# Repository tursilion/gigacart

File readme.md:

20181211

This is a largely unsorted folder that contains all source for TI-99/4A Dragon's Lair (but no copyrighted video, sorry), test code, PCB layouts for KiCad and CPLD programming for the Gigacart it ran on.

It's on the 'contact me and ask' license. ;)

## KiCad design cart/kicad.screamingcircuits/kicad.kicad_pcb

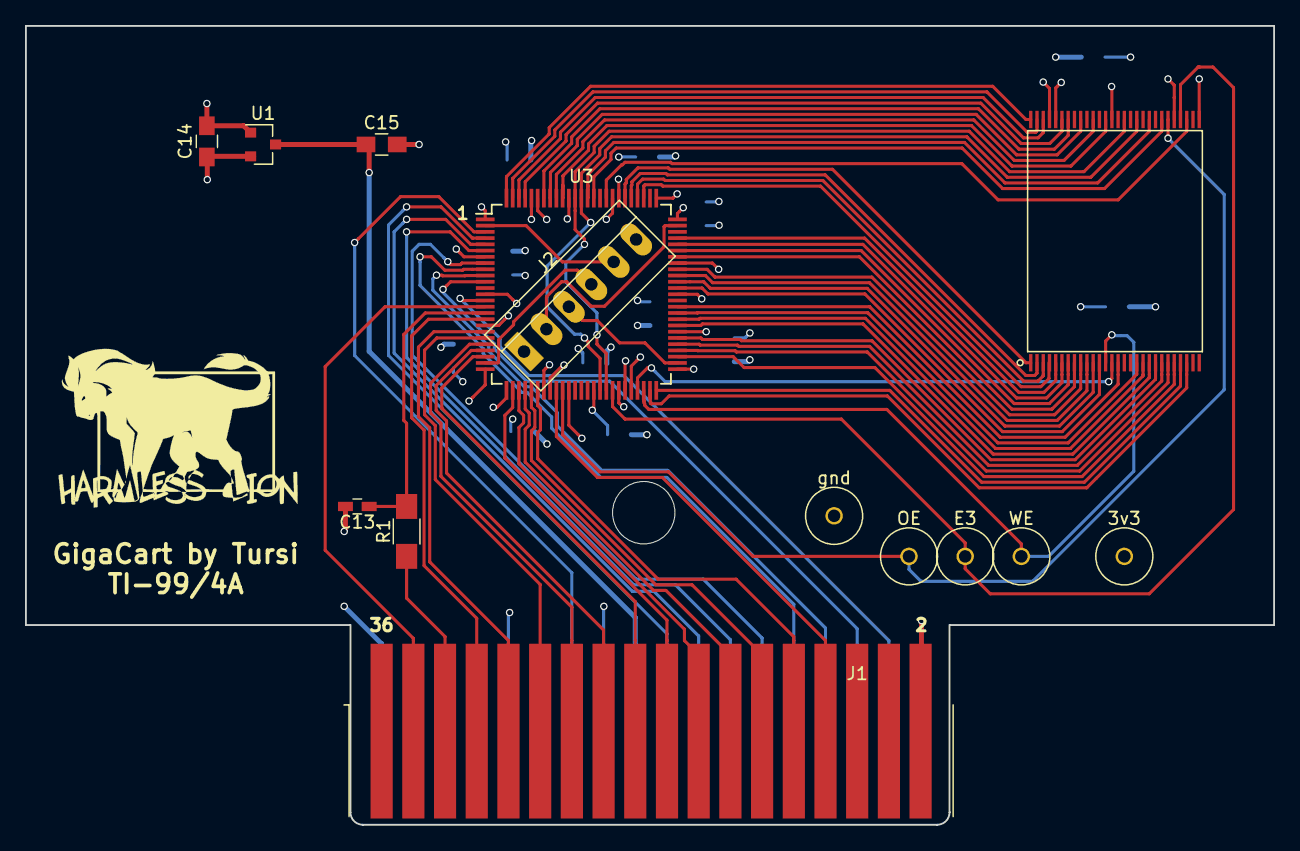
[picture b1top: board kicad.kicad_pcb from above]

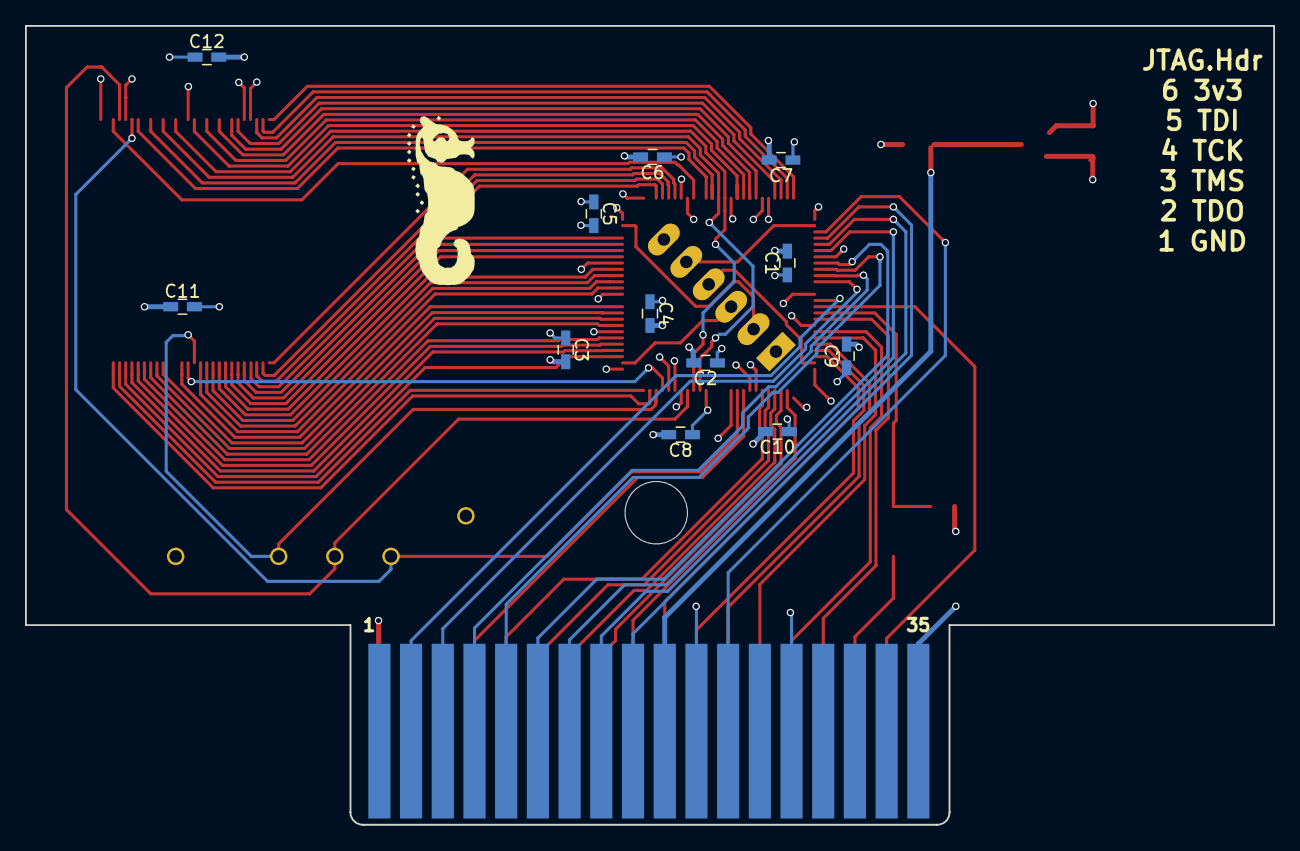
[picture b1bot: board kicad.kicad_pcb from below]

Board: 4 copper layers, 100.0 x 64.0 mm, 27 parts (13 on the bottom side), 72 nets.

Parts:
3v3: .; 1pin
.: .; LOGO_SEAHORSE
C1, C2, C3, C4, C5, C6, C7, C8, C9, C10, C11, C12, C13: 1nF; C_0603_HandSoldering
C14, C15: 1uF; C_0805_HandSoldering
E3: .; 1pin
J1: Bus_TI994A_Cart; BUS_TI99_CART
J2: Conn_01x06; PINHEAD1-6
OE: .; 1pin
R1: 47^; R_1206_HandSoldering
U1: MCP1700-3302E_SOT23; SOT-23
U2: S29GL01G-128MB-Flash; TSOP-56
U3: GigaCart_CPLD_LC4064; TQFP-100_14x14mm_Pitch0.5mm
WE: .; 1pin
gnd: .; 1pin

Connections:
+3V3: 3v3.1, C1.1, C2.1, C3.1, C4.1, C5.1, C6.1, C7.1, C8.1, C9.1, C10.1, C11.2, C12.1, C14.1, J2.6, U1.2, U2.29, U2.43, U3.13, U3.25, U3.33, U3.40, U3.45, U3.63, U3.75, U3.83, U3.90, U3.95
+5V: C15.1, J1.19, U1.3
GND: C1.2, C2.2, C3.2, C4.2, C5.2, C6.2, C7.2, C8.2, C9.2, C10.2, C11.1, C12.2, C13.2, C14.2, C15.2, J1.2, J1.35, J2.1, U2.33, U2.52, U2.53, U3.1, U3.7, U3.18, U3.26, U3.32, U3.46, U3.51, U3.57, U3.68, U3.76, U3.82, U3.96, gnd.x1
unnamed: J1.32, R1.1
unnamed: J2.2, U3.74
unnamed: J2.3, U3.52
unnamed: J2.4, U3.24
unnamed: J2.5, U3.2
unnamed: E3.1, U2.32, U3.43
unnamed: U2.13, U3.48, WE.1
unnamed: OE.1, U2.34, U3.35
unnamed: U2.1, U3.81
unnamed: U2.2, U3.80
unnamed: U2.3, U3.79
unnamed: U2.4, U3.78
unnamed: U2.5, U3.72
unnamed: U2.6, U3.71
unnamed: U2.7, U3.70
unnamed: U2.8, U3.69
unnamed: U2.9, U3.67
unnamed: U2.10, U3.66
unnamed: U2.11, U3.65
unnamed: U2.12, U3.64
unnamed: U2.14, U3.47
unnamed: U2.15, U3.61
unnamed: U2.18, U3.60
unnamed: U2.19, U3.59
unnamed: U2.20, U3.58
unnamed: U2.21, U3.56
unnamed: U2.22, U3.55
unnamed: U2.23, U3.54
unnamed: U2.24, U3.53
unnamed: U2.25, U3.50
unnamed: U2.26, U3.49
unnamed: U2.31, U3.84
unnamed: U2.54, U3.98
unnamed: U2.55, U3.99
unnamed: U2.56, U3.100
OA0: U2.51, U3.97
OD0: U2.35, U3.86
OD1: U2.37, U3.87
OD2: U2.39, U3.41, U3.88
OD3: U2.41, U3.42, U3.89
OD4: U2.44, U3.91
OD5: U2.46, U3.92
OD6: U2.48, U3.93
OD7: U2.50, U3.94
TI_A3: J1.24, U3.21
TI_A4: J1.30, U3.17
TI_A5: J1.28, U3.19
TI_A6: J1.26, U3.20
TI_A7: J1.22, U3.22
TI_A8: J1.20, U3.23
TI_A9: J1.18, U3.27
TI_A10: J1.16, U3.28
TI_A11: J1.14, U3.29
TI_A12: J1.12, U3.30
TI_A13: J1.10, U3.31
TI_A14: J1.23, U3.3
TI_A15: J1.8, U3.34
TI_D0: J1.17, U3.4
TI_D1: J1.15, U3.5
TI_D2: J1.13, U3.6
TI_D3: J1.11, U3.8
TI_D4: J1.9, U3.9
TI_D5: J1.7, U3.10
TI_D6: J1.5, U3.11
TI_D7: J1.3, U3.14
TI_GCLK: J1.27, U3.36
TI_GSEL: J1.21, U3.44
TI_ROM: J1.34, U3.15
TI_WE: C13.1, R1.2, U3.16

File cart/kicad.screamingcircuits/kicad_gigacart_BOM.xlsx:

Item # | "Quantity" | "Ref Des" | "Manufacturer" | "Mfg Part #" | "Dist. Part #" | "Description" | "Package" | "Type"
1 | 1 | U2 | Cypress Semiconductor | S29GL01GT10TFI020 | 428-3610-ND | TSOP-56 1Gb NOR flash | TSOP-56 | SMT
2 | 13 | C1,C2,C4,C5,C7,C11,C12,C13,C3,C6,C8,C9,C10 | Worth Electronics Inc | 885012006029 | 732-7771-6-ND | 1000pF 16v 0603 | C0603 | SMT
3 | 2 | C14,C15 | Kemet | C0805C105J4RACTU | 399-8001-2-ND | 1uF 16v 0805 | C0805 | SMT
4 | 1 | R1 | ROHM Semiconductor | ESR18EZPJ470 | RHM47ICT-ND | 47 ohm 1/2w 5% 1206 | R1206 | SMT
5 | 1 | U1 | Microchip | MCP1700T-3302E/TT | MCP1700T3302ETTTR-ND | LDO 250mA 3.3v output | SOT-23 | SMT
6 | 1 | U3 | Lattice | LC4064V-75TN100C | 220-1037-ND | CPLD 400 MHZ 64 Macrocell 3.3V | TQFP-100_14x14mm_Pitch0.5mm | SMT
7 | 2 | J1,J2 | n/a
Substitution for like value parts on C1-C13 (1nF, 0603, 6v or more), C14-C15 (1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
J1 and J2 have no components, DNP.

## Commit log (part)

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2018-07-02 backup commit
2018-09-17 forgot I was using git on this project... ahem. current state: CPLD operates, ROM works, GROM works without autoincrement. Autoinc is breaking the TI and not sure why!
2018-09-26 Checkpoint - grom emulation locks up the console but only if autoincrement is on - if I disable it, then GROM otherwise works correctly. Simulation looks correct. Not sure what is wrong.
2018-09-26 checkpoint: new increment method but it doesn't work. The commented out code works but loses the first increment for some reason. Going to try a new approach.
2018-09-27 Still working on getting GROM alive again... this doesn't fit but committing before I remove dead code
2018-09-27 Builds, fits, and simulates right, but the GROM side returns no data on hardware. The grmadr <= grminc is causing a combitorial loop on grmadr, which may or may not be an issue.
2018-09-30 Checkpoint
2018-10-10 Version with working GROM increment (but off by one and too large for the CPLD)
2018-10-10 IT FINALLY WORKS!
2018-10-15 -updated output with final dither and created scripts to build it -updated videostepper app for sorting -documented all frames -updated final cart schematic (not PCB yet)
2018-11-05 guess I never committed the working version...
2018-11-05 code and through-hole version of cart
2018-12-09 working with border graphics, framework in place
2018-12-12 Checkpoint - support code in place, attract mode works, F18A detect/skip working
2018-12-12 options menu implemented
2018-12-12 added success beep calculate the scratchpad loop address rather than hand edit it
2018-12-13 -Add digits, sprites, plan for tables
2018-12-15 -added new slides for attract and diagnostics -updated attract mode -added diagnostics to main -made main able to change banks on define -added placeholder for keyboard version -added diagnostics ban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
2018-12-16 -diagnostics are done -scene scripting engine is done (tested and working on drawbridge) -sprites are now built by script -cleaned up the icon help screens
2018-12-16 -hand tuned icon help screens
2018-12-16 -fixed f18A hint sprites -filled in the sequencing in the rom contents -broke up the intro scene so I can split it for arcade mode (still to retest)
2018-12-17 -broke out some defines into a common header -split scene playback into a separate bank with a common include block -updated main code and dragonostics for new layout and shared data -set up ROM base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
2018-12-18 -added 'practice' mode -minor code shuffling and cleanup
2018-12-19 -comment updates -add 9938 reg 8-15 init (was it needed? probably not?) -don't score starting 49 points in easy mode -don't score at all in practice mode -set f18a flag before calling bitmap init so 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
2018-12-21 -split drawbridge and vestible -used a codegen to create templates for the remaining scenes (to be filled in)
2018-12-24 First pass of all scene data...
2018-12-26 Remove vestible from the drawbridge. Implement the arcade sequencing. start the home sequencing.
2018-12-27 Checkpoint commit - code for sequencing in place and builds. Not tested
2018-12-27 -A few minor scene updates -Arcade and home play loops tested through, lots of notes but basically working
2018-12-29 -pool balls and vines are still unplayably broken -software audit of all scene movements and tables -practice halts on hint instead of valid input -fix score adds (maybe, not tested) -default to arca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
2019-01-02 -added win screen and thanks screen -changed arrows on instruction screen to a sprite table and redid backgrounds -fix arcade/home toggle -remove unused ADDSCORE from main code bank -fix alpha lock u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
2019-01-03 -tested scene playout after input - unsatisfactory. Some unused code for it remains. -fixed joystick edge detection, easier than expected, feels better with it in -fixed duration of input beep in ret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
2019-01-04 -add continue on failure to the diagnostics -make diagnostics tones louder -change game beep to slightly softer and lower pitch to match arcade low pitch tone -copied into keyboard again (still not u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
2019-01-05 -Moved Diagnostics bank test screens to sub 32MB (actually sub-64k) to improve usefulness -Dragonostics now self-inits graphics and SIT -added custom border graphics for Diagnostics and implemented p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
2019-01-07 Updated reset mechanism on CPLD to be tied to GROM selection. A bit hacky, but it appears to work better.
2019-01-07 -fix cartpage on all scenes to account for the new shift. game works again
2019-01-09 -move scene equates into commoncode -turn down volume of beeps again -display correct frame for win screen -implement keyboard version -
2019-01-27 -Added arcade version of river scene -added intro copyright screen -added secret scene select (joystick mode only, hold up leaving config menu) -swapped test for end of video and page increment - thi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
2019-01-31 add test code
2019-02-12 -CPLD updates
2019-03-16 checkpoint - new cart not working yet
2019-03-17 Cart writing functions are working, at least in test mode
2019-03-18 fixes found so far...
2019-03-22 -build in an 128k offset till the first page of useful data -fix illegal opcode on entry to Dragonostics -fix sprites not clearing after keyboard test in Dragonostics -tweak up the program load to us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
2019-03-24 -update cartwriter to use scratchpad loops for more speed -fix bug with running man that caused him to update every cycle
2019-03-26 -changed seahorse load back to pull-up (drive OE low) -add checksum to cartWriter (to check ROM checksum) -add a few missing volatiles to cartWriter -fix Dragonostics advanced screen to start on page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
2019-03-26 Minor cleanup of the seahorse load. Changed reset pin back to slow slew.
2019-04-07 -add CPLD and CartWrite changes for experimental board that manages CE instead of Reset
2020-10-16 - pushing schematic PDF and all the changes GIT said were there that I don't remember what they were ;)
2022-01-25 - add readme
2022-01-25 - create a dist folder pointing to the repo
2022-01-27 remove empty dist folder
2024-12-17 - added building.txt
2026-02-13 - some missing tools added
2026-02-14 - more updates, adding missing utilities, replacing debug builds with release builds for custom tools
2026-02-15 - adding missing tools and dl_pics output files
2026-02-15 add license - or rather, expressly confirm no license is granted
2026-02-15 - add missing boot binary
